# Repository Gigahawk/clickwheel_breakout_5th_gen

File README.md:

# iPod Clickwheel Breakout
Breakout board for an iPod 5th Gen (Video) clickwheel

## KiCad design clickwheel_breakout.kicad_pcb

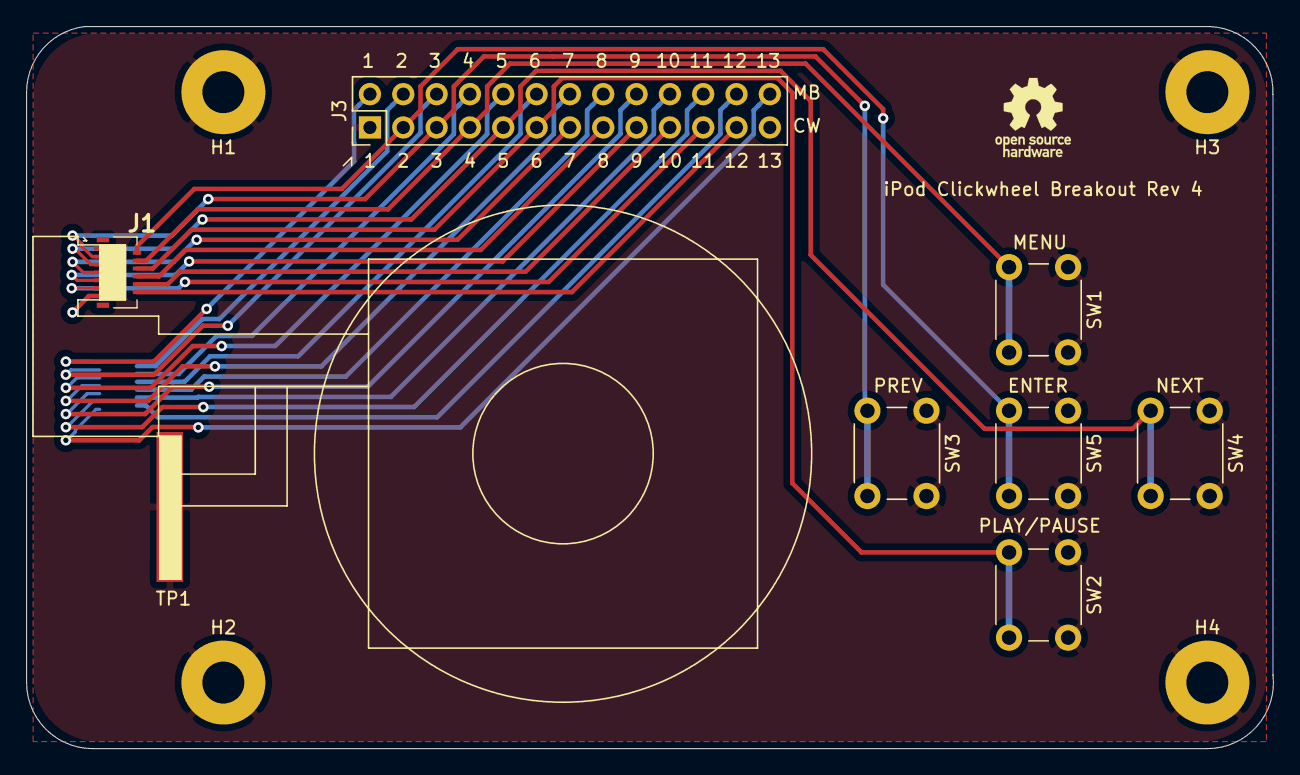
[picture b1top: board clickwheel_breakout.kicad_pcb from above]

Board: 2 copper layers, 95.0 x 55.0 mm, 13 parts (1 on the bottom side), 26 nets.

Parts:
H1, H2, H3, H4: MountingHole_Pad; MountingHole_3.2mm_M3_Pad
J1, J2: 1-2328724-3; 123287243
J3: Conn_02x13_Odd_Even; PinHeader_2x13_P2.54mm_Vertical
SW1: MENU; SW_PUSH_6mm
SW2: ▶ ||; SW_PUSH_6mm_H4.3mm
SW3: |◀◀; SW_PUSH_6mm_H4.3mm
SW4: ▶▶|; SW_PUSH_6mm_H4.3mm
SW5: ENTER; SW_PUSH_6mm_H4.3mm
TP1: ClickWheel Ground Pad; clickwheel

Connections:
GND: H1.1, H2.1, H3.1, H4.1, J1.1, J3.1, SW1.1, SW2.1, SW3.1, SW4.1, SW5.1, TP1.1
GND_MB: J2.13, J3.2
P1_0_CW: J1.12, J3.23
P1_0_MB: J2.2, J3.24
P1_1_CW: J1.11, J3.21
P1_1_MB: J2.3, J3.22
P1_3_CW: J1.10, J3.19
P1_3_MB: J2.4, J3.20
P1_5_CW: J1.9, J3.17
P1_5_MB: J2.5, J3.18
P1_7_CW: J1.8, J3.15
P1_7_MB: J2.6, J3.16
P3_1_CW: J1.7, J3.13
P3_1_MB: J2.7, J3.14
PB_DOWN_CW: J1.6, J3.11, SW2.2
PB_DOWN_MB: J2.8, J3.12
PB_LEFT_CW: J1.3, J3.5, SW3.2
PB_LEFT_MB: J2.11, J3.6
PB_MID_CW: J1.2, J3.3, SW5.2
PB_MID_MB: J2.12, J3.4
PB_RIGHT_CW: J1.5, J3.9, SW4.2
PB_RIGHT_MB: J2.9, J3.10
PB_UP_CW: J1.4, J3.7, SW1.2
PB_UP_MB: J2.10, J3.8
VCC: J1.13, J3.25
VCC_MB: J2.1, J3.26

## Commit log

2020-06-21 Add preview image
2020-06-21 Flip passthrough connector, add button silkscreens
2020-06-23 Round PCB corners
2020-07-07 Switch to 2 row header to allow control of which lines are connected to mainboard
2020-07-09 Add OSHW logo, update preview
2020-07-09 Subtract silkscreen from copper in gerber export
2020-08-03 Move JLCPCB order number location
